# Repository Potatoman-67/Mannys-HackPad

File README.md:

# Mannys-HackPad
A overview of everything about my HackPad  
This is my first project that i have started that includes electronics such as pbc's

This Hackpad features:  
* 6 Keys  
* OLED 0.91" Diplay  
* Rotary Encoder  
* 2 LED Lights  
* Custom PBC
* Microcontroller

BOM:https://1drv.ms/x/c/aecf50bb8b6a1a51/IQBHk3moHp4gQo3GZcMQS4z-AadAGAVgVA1_fGxTUaH48ak?e=pv6D1j

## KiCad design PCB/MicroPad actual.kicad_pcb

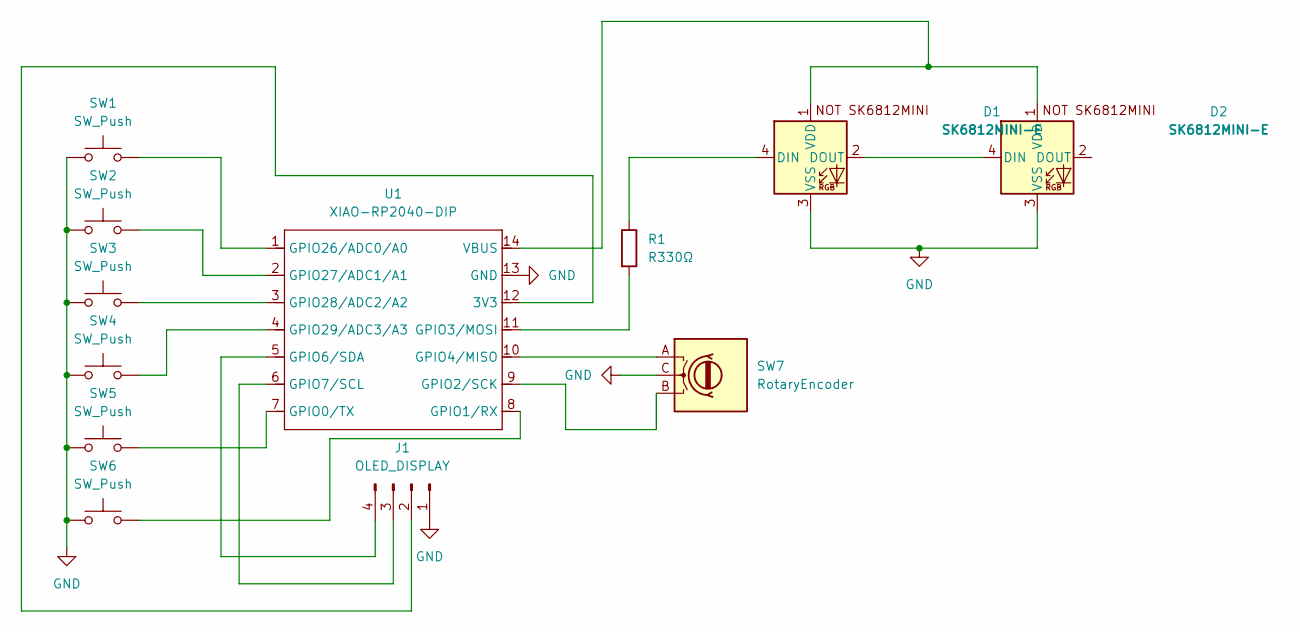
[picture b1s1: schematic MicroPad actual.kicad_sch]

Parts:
D1, D2: SK6812MINI-E; MX_SK6812MINI-E_REV (1)
J1: OLED_DISPLAY; PinHeader_1x04_P2.54mm_Vertical
R1: R330Ω
SW1, SW2, SW3, SW4, SW5, SW6: SW_Push; SW_Cherry_MX_1.00u_PCB
SW7: RotaryEncoder; RotaryEncoder_Alps_EC11E-Switch_Vertical_H20mm_CircularMoun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
U1: XIAO-RP2040-DIP

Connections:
GND: D1.3 (VSS), D2.3 (VSS), J1.1, SW1.1, SW2.1, SW3.1, SW4.1, SW5.1, SW6.1, SW7.C, U1.13 (GND)
unnamed: D1.4 (DIN), R1.1
unnamed: D1.2 (DOUT), D2.4 (DIN)
unnamed: D1.1 (VDD), D2.1 (VDD), U1.14 (VBUS)
unnamed: J1.2, U1.12 (3V3)
unnamed: J1.3, U1.6 (GPIO7/SCL)
unnamed: J1.4, U1.5 (GPIO6/SDA)
unnamed: SW5.2, U1.7 (GPIO0/TX)
unnamed: SW6.2, U1.8 (GPIO1/RX)
unnamed: SW7.B, U1.9 (GPIO2/SCK)
unnamed: R1.2, U1.11 (GPIO3/MOSI)
unnamed: SW7.A, U1.10 (GPIO4/MISO)
unnamed: SW1.2, U1.1 (GPIO26/ADC0/A0)
unnamed: SW2.2, U1.2 (GPIO27/ADC1/A1)
unnamed: SW3.2, U1.3 (GPIO28/ADC2/A2)
unnamed: SW4.2, U1.4 (GPIO29/ADC3/A3)

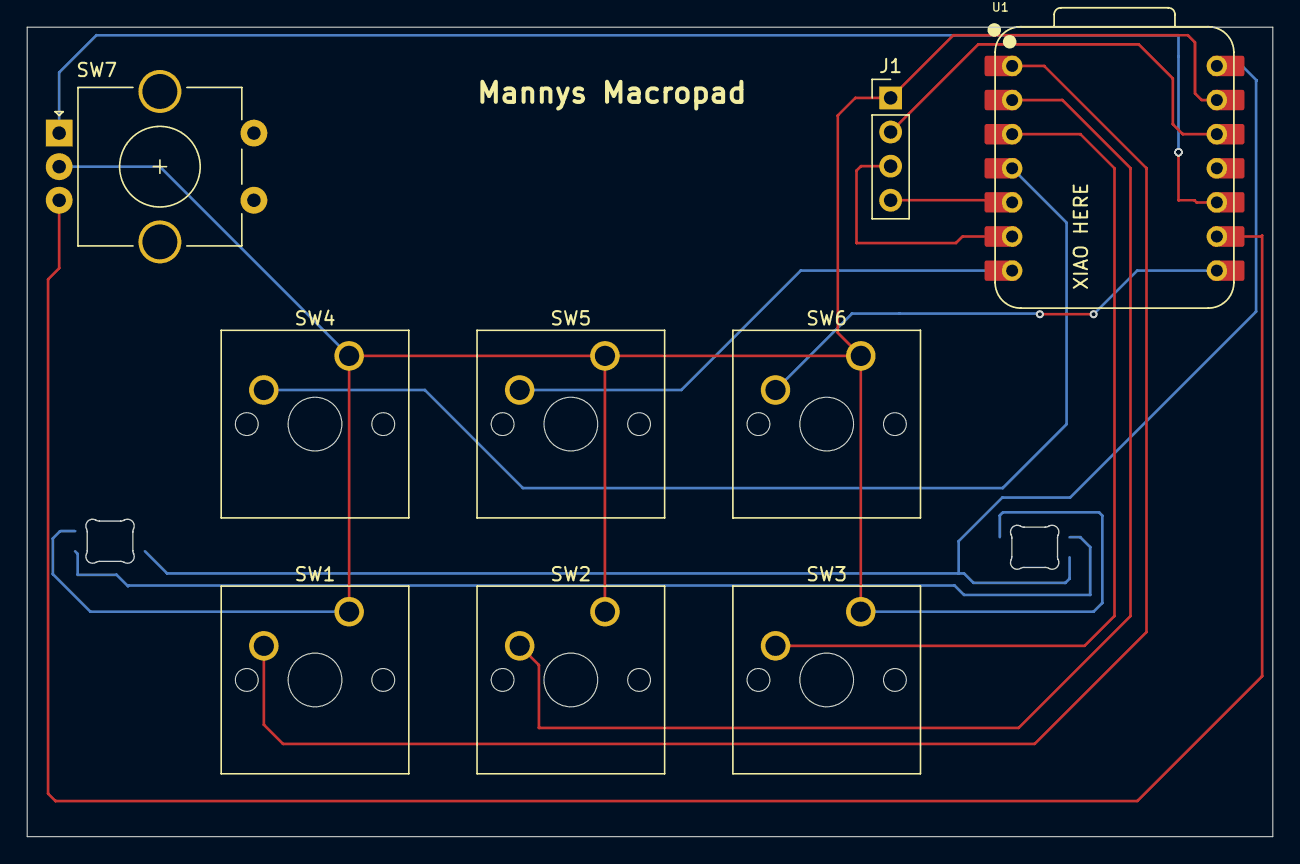
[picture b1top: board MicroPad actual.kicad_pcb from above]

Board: 2 copper layers, 92.7 x 60.2 mm, 11 parts (0 on the bottom side), 14 nets.

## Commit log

2026-01-19 Create PCB
2026-01-19 Create CAD
2026-01-20 Create tmn
2026-01-20 Create temp
2026-03-05 Create Gerbers
